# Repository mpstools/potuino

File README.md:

potuino
=======

Very flexible arduino shield for a programmable contactless potentiometer. The shield includes a sensor and a magnet holder pcb for break-out to get startet within seconds. This Potuino shield is compatible with Arduino Uno. 
The pcb was designed using eagle and includes an break-out to make a magnetholder.

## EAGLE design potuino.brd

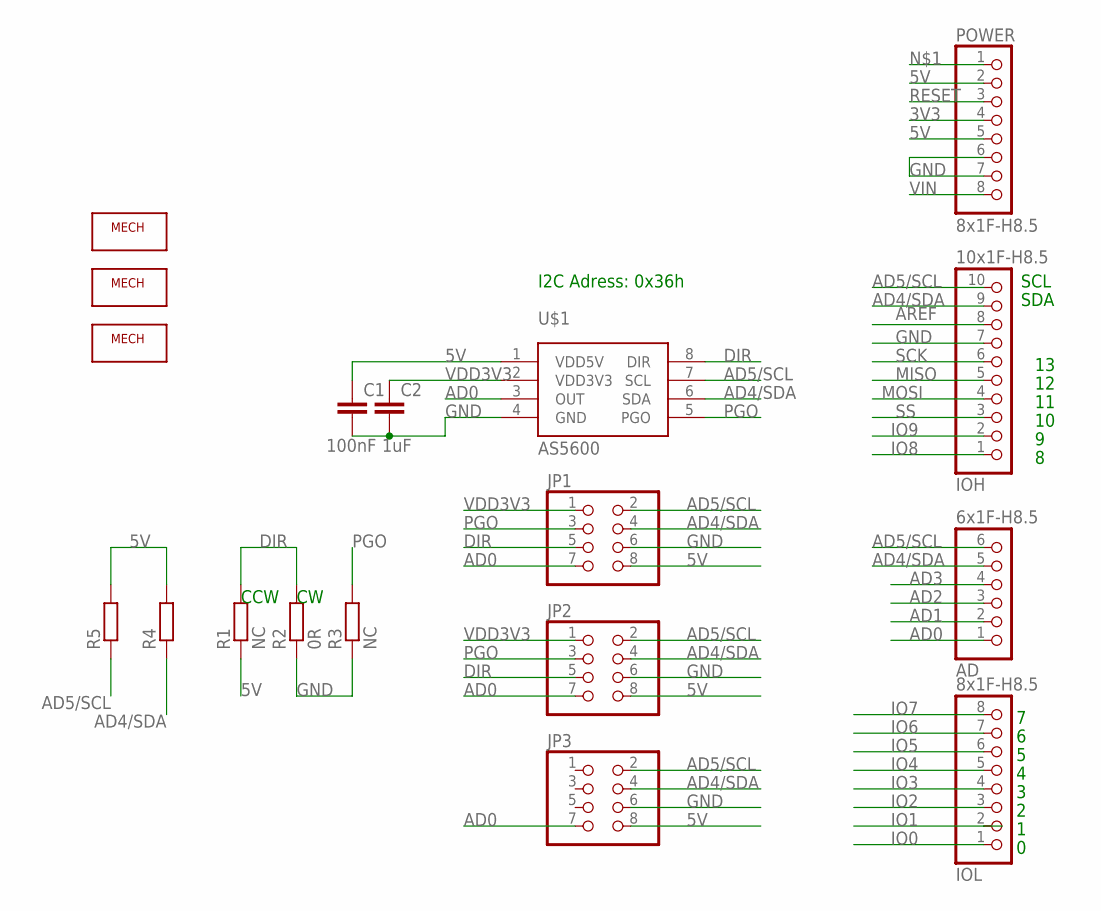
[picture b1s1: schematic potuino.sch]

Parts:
AD: 6x1F-H8.5; 1X06
C1: 100nF; C0805
C2: 1uF; C0805
IOH: 10x1F-H8.5; 1X10
IOL: 8x1F-H8.5; 1X08
JP1, JP2, JP3: PINHD-2X04_2.54; 2X04
POWER: 8x1F-H8.5; 1X08
R1, R3: NC; R0603
R2: 0R; R0603
R4, R5: R-EU_R0603; R0603
U$1: AS5600; SO08
U$2, U$3: MECHANICAL; MECHANICAL-PARTS
U$4: MECHANICAL2; MECHANICAL-TOP

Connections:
3V3: POWER.4
5V: C1.1, JP1.8, JP2.8, JP3.8, POWER.2, POWER.5, R1.1, R4.2, R5.2, U$1.1 (VDD5V)
AD0: AD.1, JP1.7, JP2.7, JP3.7, U$1.3 (OUT)
AD1: AD.2
AD2: AD.3
AD3: AD.4
AD4/SDA: AD.5, IOH.9, JP1.4, JP2.4, JP3.4, R4.1, U$1.6 (SDA)
AD5/SCL: AD.6, IOH.10, JP1.2, JP2.2, JP3.2, R5.1, U$1.7 (SCL)
AREF: IOH.8
DIR: JP1.5, JP2.5, R1.2, R2.2, U$1.8 (DIR)
GND: C1.2, C2.2, IOH.7, JP1.6, JP2.6, JP3.6, POWER.6, POWER.7, R2.1, R3.1, U$1.4 (GND)
IO0: IOL.1
IO1: IOL.2
IO2: IOL.3
IO3: IOL.4
IO4: IOL.5
IO5: IOL.6
IO6: IOL.7
IO7: IOL.8
IO8: IOH.1
IO9: IOH.2
MISO: IOH.5
MOSI: IOH.4
PGO: JP1.3, JP2.3, R3.2, U$1.5 (PGO)
RESET: POWER.3
SCK: IOH.6
SS: IOH.3
VDD3V3: C2.1, JP1.1, JP2.1, U$1.2 (VDD3V3)
VIN: POWER.8

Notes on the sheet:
SDA
SCL
CCW
I2C Adress: 0x36h

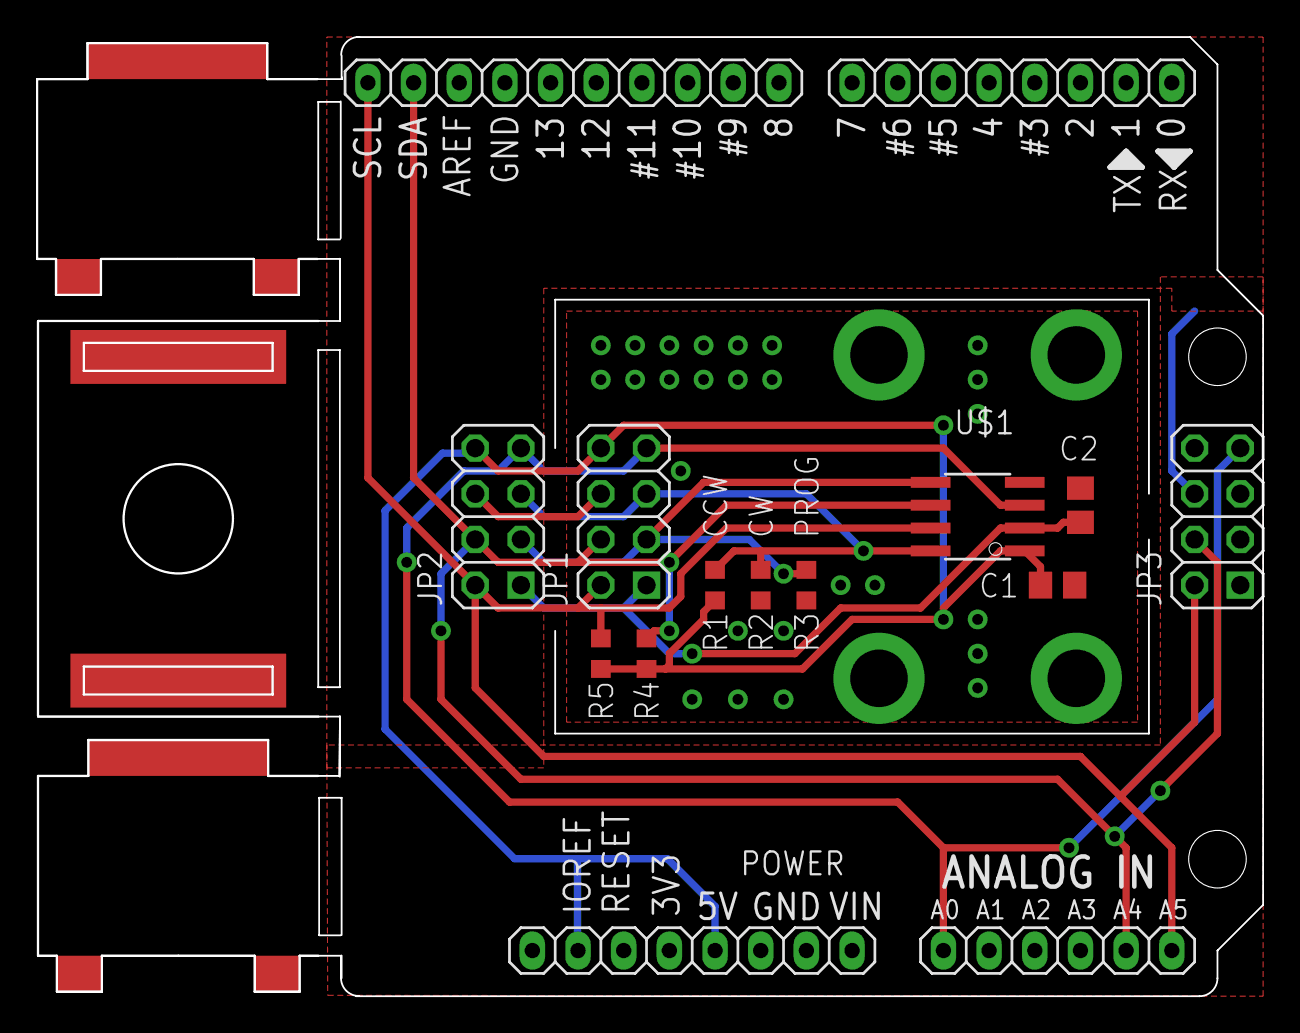
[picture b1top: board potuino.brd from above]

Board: 2 copper layers, 68.2 x 53.3 mm, 18 parts (0 on the bottom side), 8 nets.

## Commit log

2014-06-30 Initial board files
    potuino 1v3
